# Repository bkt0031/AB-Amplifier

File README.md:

# Class AB Monaural 2 Watt Amplifier

With regards to class AB audio amplifiers there is really nothing new under the sun, and this design is no exception.

I have a collection of amateur radio transceivers I built as kits from QRP Labs that the audio ouput can only drive small
headphones (earbuds). Personally I cannot stand having earbuds in my ears for long durations, so I wanted to make an
audio amplifier to drive a speaker I reprovisioned from a commercial mobile radio. 

My requirements for the audio amplifier was:

* Run off of a 12 VDC, single rail, power supply
* Drive a 4 Ohm speaker
* Loud enough for a typical size room with enough volume to overcome any incidental noise/sounds
* Needs to be an analog class of operation - please, no switching...
* I don't want to waste power - needs efficiency
* Power switch
* Power input on a 2.1x5.5 mm panel jack
* Power indicator
* Volume control

Loudness requirements is a bit nebulous to me as I have no clue as to how the sound pressure levels from
the speaker relate to the wattage applied to the speaker. In this case I decided to just go for the maximum
that I could get from a 12 VDC single rail supply, which I know is not much really in my way of thinking.

My general conclusion is to use a class AB amplfier, and the ultimate circuit I ended up with is
based on the design of *The Tube Roaster* channel on [YouTube](https://www.youtube.com/watch?v=THRFZiEfnnA). 
The largest difference was the supply voltage he was using and my 12 VDC supply requirement. I ended
up entering the circuit in [QSpice](https://www.qorvo.com/design-hub/design-tools/interactive/qspice/), tweaking
the bias resistors till I got even clipping on the output. The resulting circuit looks like:

The net simulate results were maximum unclipped output voltage across the 4 Ohm load of 8.1 Vp-p which results in around
2 Watts being delivered to the load. The simulated unclipped gain was 23.1 dB at 1 KHz.

The only oddity of this circuit is the boostrapping capacitor C4. Based on what little I know about boostrapping it has
the effect of reducing the AC current through R7 which effectively raises the collector AC resistance on the input common-emitter
amplifier (Q1). Running the simulation with and without C4 show the gain to increase around 3 dB with the bootstrapping circuit
in place.

After building this circuit I ended up with about 8.23 Vp-p unclipped maximum output voltage which will deliver 2.1 Watts to
the 4 Ohm speaker.

## External Case Mounted Parts

| Qty   | Description                       | Distributor  | Part Number          | Notes                |
| :---- | :-------------------------------- | :----------- | :------------------- | :------------------- |
| 1     | POT 1K OHM 1/2W PLASTIC LINEAR    | Digi-Key     | 53AAD-B28-B10L-ND    | Overkill - lol       |
| 1     | Toggle Switch SPST Panel Mount    | Digi-Key     | 360-MN11ES1W01-ND    |                      |
| 1     | LED 3MM PANEL MNT W/24AWG LEADS   | Digi-Key     | SSI-LXR3612ID-150-ND |                      |
| 1     | CONN JACK MONO 3.5MM PNL MNT      | Digi-Key     | SC1455-ND            |                      |
| 1     | CONN RCA JACK MONO 3.2MM PNL MT   | Digi-Key     | CP-1412-ND           | No locating features |
| 1     | CONN PWR JACK 2.0X5.5MM SOLDER    | Digi-Key     | CP-5-ND              |                      |

## PCB Layout

## Amplifier Enclosure

The case was printed using ABS filament. I always have a problem with determining hole size for the threaded heat
inserts. In my case the standoff hole sizes were a tad small and I needed to increase the hole size so that 
the head insert would go in without deforming the standoff.

## Future Ideas
* Mute button
* Headphone jack integration
* Use surface mount components to reduce size
* Smaller output transistors and heatsinks. In the current design these are barely getting warm at full power output

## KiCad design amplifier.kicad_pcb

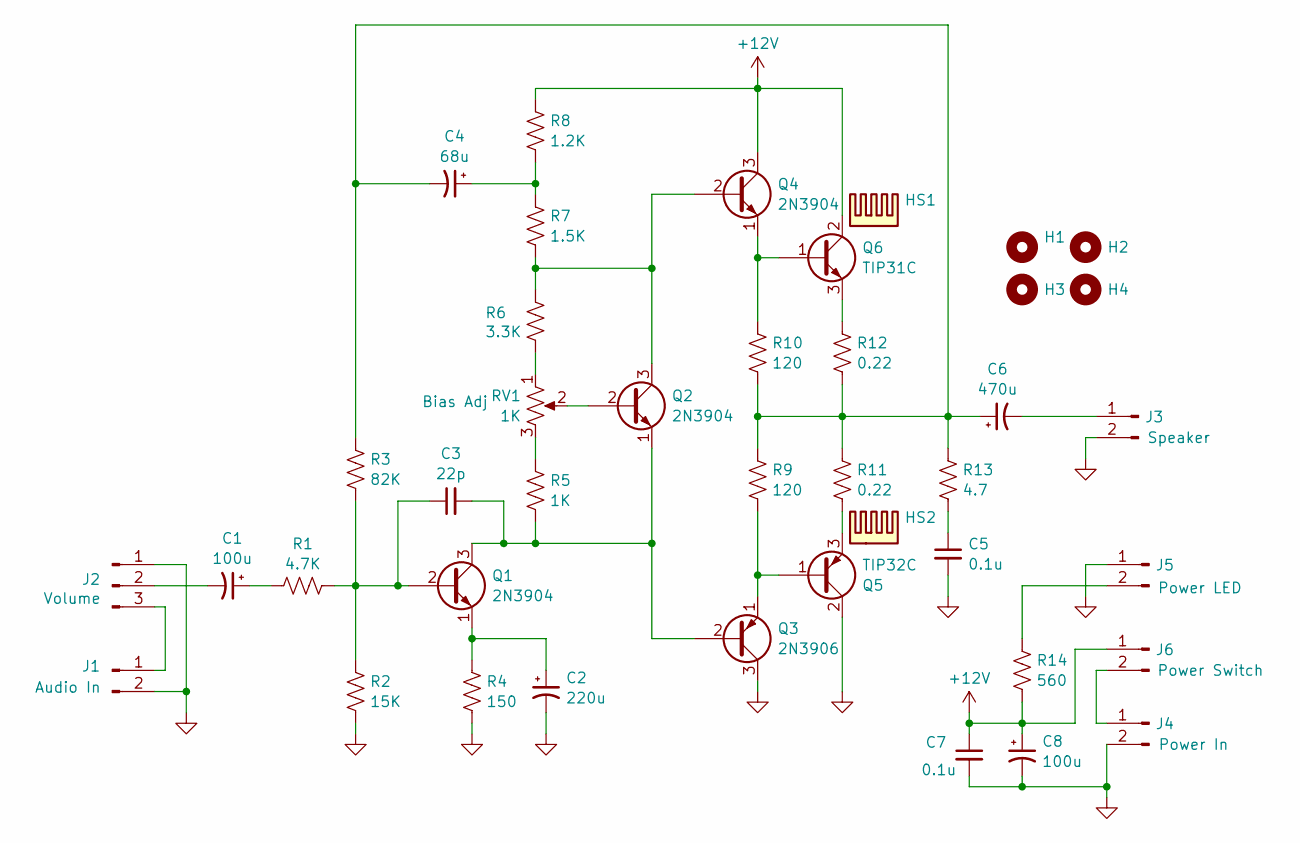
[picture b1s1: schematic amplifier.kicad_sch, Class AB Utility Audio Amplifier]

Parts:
C1, C8: 100u; CP_Radial_D5.0mm_P2.00mm; PartNo 1572-1659-ND
C2: 220u; CP_Radial_D6.3mm_P2.50mm; PartNo 1572-1705-ND
C3: 22p; C_Rect_L4.0mm_W2.5mm_P2.50mm; PartNo BC5146-ND
C4: 68u; CP_Radial_D5.0mm_P2.00mm; PartNo 1189-2243-ND
C5, C7: 0.1u; C_Rect_L4.0mm_W2.5mm_P2.50mm; PartNo BC1084TR-ND
C6: 470u; CP_Radial_D10.0mm_P5.00mm; PartNo 399-18264-1-ND
H1, H2, H3, H4: MountingHole; MountingHole_3.2mm_M3_ISO7380
HS1, HS2: Heatsink; Aavid_531002B00000G_35x13mm; PartNo HS231-ND
J1, J5: 2 Pos; JST_PH_B2B-PH-K_1x02_P2.00mm_Vertical; PartNo 455-1704-ND
J2: 3 Pos; JST_PH_B3B-PH-K_1x03_P2.00mm_Vertical; PartNo 455-B3B-PH-KL-ND
J3, J4, J6: 2 Pos; JST_XH_B2B-XH-A_1x02_P2.50mm_Vertical; PartNo 455-B2B-XH-A-ND
Q1, Q2, Q4: 2N3904; TO-92; PartNo 497-2395-ND
Q3: 2N3906; TO-92; PartNo 497-2404-ND
Q5: TIP32C; TO-220-3_Vertical; PartNo 497-2628-5-ND
Q6: TIP31C; TO-220-3_Vertical; PartNo 497-2615-5-ND
R1: 4.7K; R_Axial_DIN0207_L6.3mm_D2.5mm_P10.16mm_Horizontal; PartNo 13-MFR-25FTE52-4K7CT-ND
R2: 15K; R_Axial_DIN0207_L6.3mm_D2.5mm_P10.16mm_Horizontal; PartNo 13-MFR-25FTE52-15KCT-ND
R3: 82K; R_Axial_DIN0207_L6.3mm_D2.5mm_P10.16mm_Horizontal; PartNo 13-MFR25SFTE52-82KCT-ND
R4: 150; R_Axial_DIN0207_L6.3mm_D2.5mm_P10.16mm_Horizontal; PartNo 13-MFR-25FTE52-150RCT-ND
R5: 1K; R_Axial_DIN0207_L6.3mm_D2.5mm_P10.16mm_Horizontal; PartNo 13-MFR-25FRF52-1KTR-ND
R6: 3.3K; R_Axial_DIN0207_L6.3mm_D2.5mm_P10.16mm_Horizontal; PartNo 13-MFR-25FTE52-3K3CT-ND
R7: 1.5K; R_Axial_DIN0207_L6.3mm_D2.5mm_P10.16mm_Horizontal; PartNo 13-MFR-25FTE52-1K5CT-ND
R8: 1.2K; R_Axial_DIN0207_L6.3mm_D2.5mm_P10.16mm_Horizontal; PartNo 13-MFR-25FTE52-1K2CT-ND
R9, R10: 120; R_Axial_DIN0207_L6.3mm_D2.5mm_P10.16mm_Horizontal; PartNo 13-MFR-25FTE52-120RCT-ND
R11, R12: 0.22; R_Axial_DIN0207_L6.3mm_D2.5mm_P10.16mm_Horizontal; PartNo 13-MFR-25FTF52-0R22CT-ND
R13: 4.7; R_Axial_DIN0207_L6.3mm_D2.5mm_P10.16mm_Horizontal; PartNo 13-MFR-25FTE52-4R7CT-ND
R14: 560; R_Axial_DIN0207_L6.3mm_D2.5mm_P10.16mm_Horizontal; PartNo 13-MFR-25FTE52-560RCT-ND
RV1: 1K; Potentiometer_Nidec_CT-6_Vertical; PartNo 563-CT-6EP102-ND

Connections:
+12V: C7.1, C8.1, J6.1, Q4.3 (C), Q6.2 (C), R8.1, R14.2
GND: C2.2, C5.2, C7.2, C8.2, J1.2, J2.1, J3.2, J4.2, J5.1, Q3.3 (C), Q5.2 (C), R2.2, R4.2
unnamed: C1.1, R1.2
unnamed: C4.1, R7.1, R8.2
unnamed: C4.2, C6.1, R3.1, R9.1, R10.1, R11.1, R12.2, R13.1
unnamed: C5.1, R13.2
unnamed: J1.1, J2.3
unnamed: C1.2, J2.2
unnamed: C6.2, J3.1
unnamed: J4.1, J6.2
unnamed: J5.2, R14.1
unnamed: C3.1, Q1.2 (B), R1.1, R2.1, R3.2
unnamed: C3.2, Q1.3 (C), Q2.1 (E), Q3.2 (B), R5.2
unnamed: C2.1, Q1.1 (E), R4.1
unnamed: Q2.2 (B), RV1.2
unnamed: Q2.3 (C), Q4.2 (B), R6.1, R7.2
unnamed: Q3.1 (E), Q5.1 (B), R9.2
unnamed: Q4.1 (E), Q6.1 (B), R10.2
unnamed: Q5.3 (E), R11.2
unnamed: Q6.3 (E), R12.1
unnamed: R5.1, RV1.3
unnamed: R6.2, RV1.1

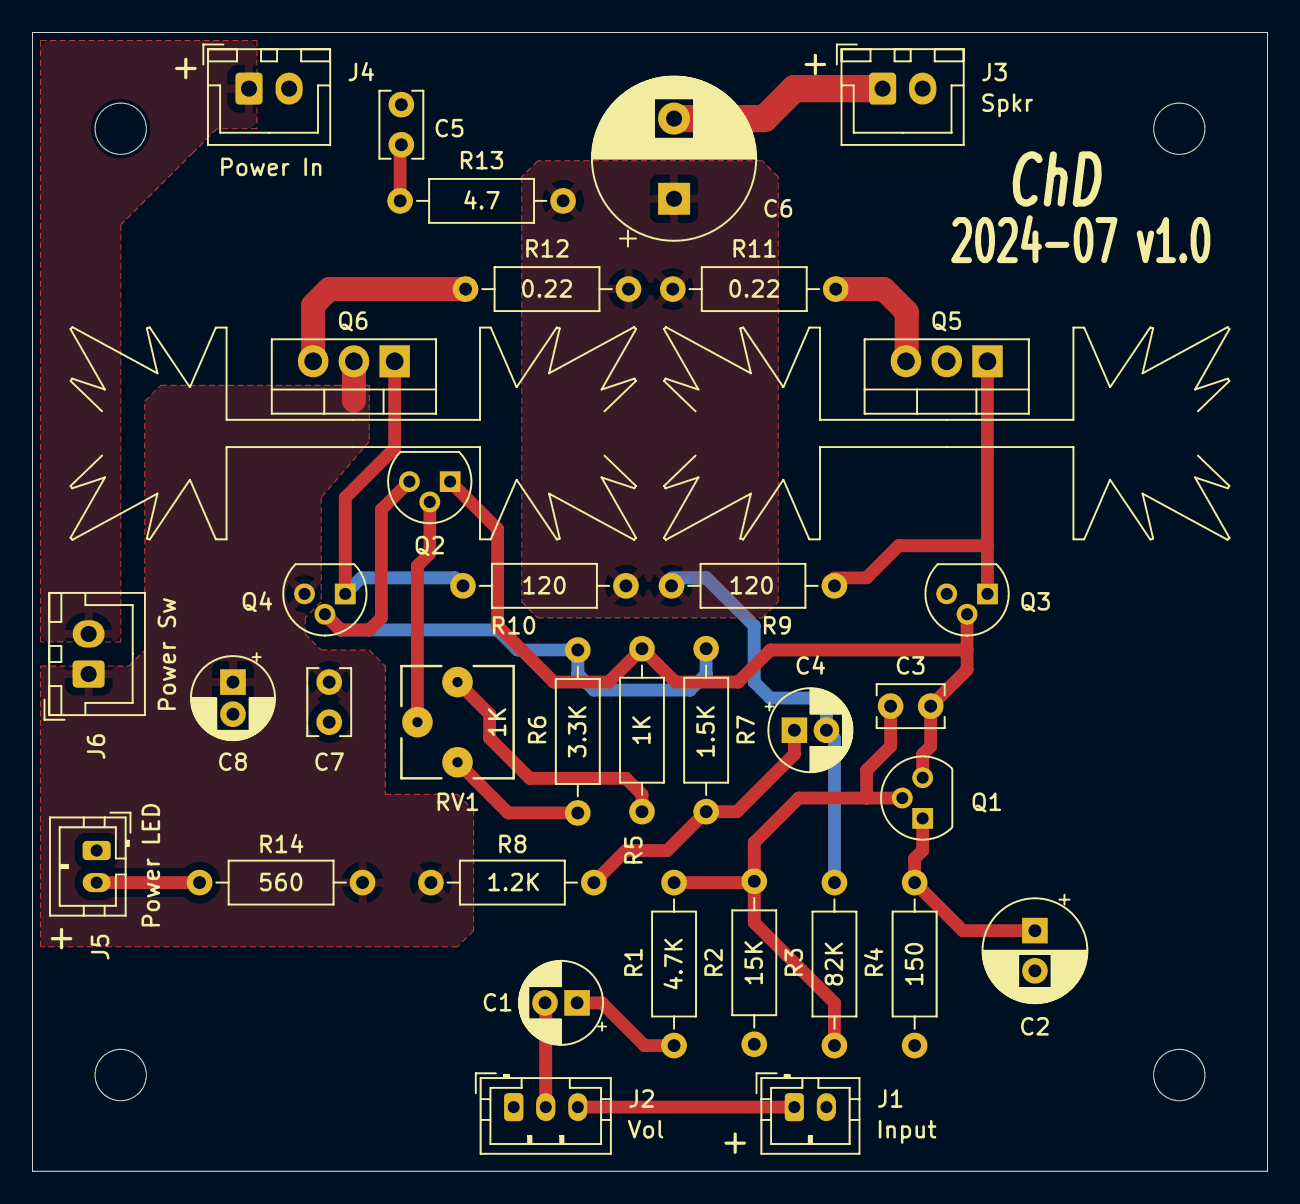
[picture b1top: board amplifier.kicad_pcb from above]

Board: 2 copper layers, 77.0 x 71.0 mm, 41 parts (0 on the bottom side), 22 nets.

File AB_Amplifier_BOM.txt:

Qty	Reference	Description	Value	WVDC	Distributor	PartNo
1	C2	CAP ALUM 220UF 20% 25V RADIAL TH	220u	25	DigiKey	1572-1705-ND
1	C3	CAP CER 22PF 50V C0G/NP0 RADIAL	22p	50	DigiKey	BC5146-ND
1	C4	CAP ALUM 68UF 20% 25V RADIAL	68u	25	DigiKey	1189-2243-ND
1	C6	CAP ALUM 470UF 20% 25V RADIAL	470u	25	DigiKey	399-18264-1-ND
2	C1,C8	CAP ALUM 100UF 20% 25V RADIAL TH	100u	25	DigiKey	1572-1659-ND
2	C5,C7	CAP CER 0.1UF 50V X7R RADIAL	0.1u	50	DigiKey	BC1084TR-ND
2	HS1,HS2	HEATSINK TO-220 BLACK 1"	Heatsink		DigiKey	HS231-ND
1	J2	CONN HEADER VERT 3POS 2MM	3 Pos		DigiKey	455-B3B-PH-KL-ND
2	J1,J5	CONN HEADER VERT 2POS 2MM	2 Pos		DigiKey	455-1704-ND
3	J3,J4,J6	CONN HEADER VERT 2POS 2MM	2 Pos		DigiKey	455-B2B-XH-A-ND
1	Q3	TRANS PNP 40V 0.2A TO92	2N3906		DigiKey	497-2404-ND
1	Q5	TRANS PNP 100V 3A TO220	TIP32C		DigiKey	497-2628-5-ND
1	Q6	TRANS NPN 100V 3A TO220	TIP31C		DigiKey	497-2615-5-ND
3	Q1,Q2,Q4	BJT TO92 40V NPN 0.625W 150C	2N3904		DigiKey	497-2395-ND
1	R1	RES 4.7K OHM 1% 1/4W AXIAL	4.7K		DigiKey	13-MFR-25FTE52-4K7CT-ND
1	R2	RES 15K OHM 1% 1/4W AXIAL	15K		DigiKey	13-MFR-25FTE52-15KCT-ND
1	R3	RES 82K OHM 1% 1/4W AXIAL	82K		DigiKey	13-MFR25SFTE52-82KCT-ND
1	R4	RES 150 OHM 1% 1/4W AXIAL	150		DigiKey	13-MFR-25FTE52-150RCT-ND
1	R5	RES 1K OHM 1% 1/4W AXIAL	1K		DigiKey	13-MFR-25FRF52-1KTR-ND
1	R6	RES 3.3K OHM 1% 1/4W AXIAL	3.3K		DigiKey	13-MFR-25FTE52-3K3CT-ND
1	R7	RES 1.5K OHM 1% 1/4W AXIAL	1.5K		DigiKey	13-MFR-25FTE52-1K5CT-ND
1	R8	RES 1.2K OHM 1% 1/4W AXIAL	1.2K		DigiKey	13-MFR-25FTE52-1K2CT-ND
1	R13	RES 4.7 OHM 1% 1/4W AXIAL	4.7		DigiKey	13-MFR-25FTE52-4R7CT-ND
1	R14	RES 560 OHM 1% 1/4W AXIAL	560		DigiKey	13-MFR-25FTE52-560RCT-ND
2	R11,R12	RES 0.22 OHM 1% 1/4W AXIAL	0.22		DigiKey	13-MFR-25FTF52-0R22CT-ND
2	R9,R10	RES 120 OHM 1% 1/4W AXIAL	120		DigiKey	13-MFR-25FTE52-120RCT-ND
1	RV1	TRIMMER 1K OHM 0.5W PC PIN TOP	1K		DigiKey	563-CT-6EP102-ND

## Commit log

2024-09-15 Initial release
